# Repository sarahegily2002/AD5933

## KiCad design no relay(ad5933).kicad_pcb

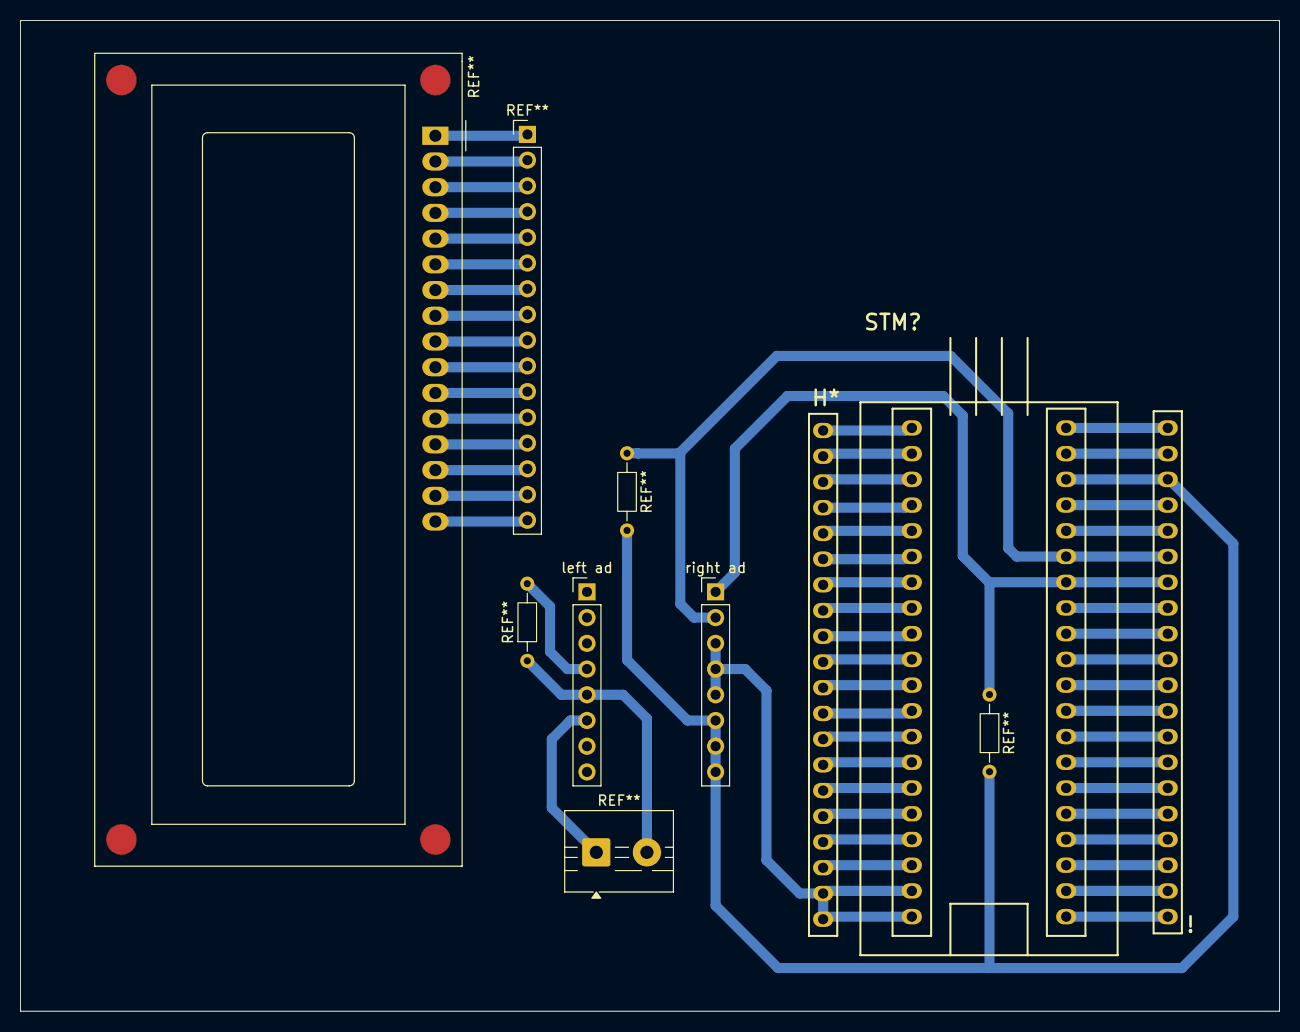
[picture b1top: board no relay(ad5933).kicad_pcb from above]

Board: 2 copper layers, 124.3 x 97.8 mm, 5 parts (0 on the bottom side), 38 nets.

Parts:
H*: FEMALE_HEADER_20; Female_Header_20
STM?: STM32
i: FEMALE_HEADER_20; Female_Header_20
left ad: 2; PinHeader_1x08_P2.54mm_Vertical
right ad: 1; PinHeader_1x08_P2.54mm_Vertical

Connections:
NetH*_1: H*.1, H*.2, STM?.GND, i.2, right ad.GND
NetH*_3: H*.3, STM?.3V3
NetH*_4: H*.4, STM?.RES
NetH*_5: H*.5, STM?.PB_11
NetH*_6: H*.6, STM?.PB_10
NetH*_7: H*.7, STM?.PB_1
NetH*_8: H*.8, STM?.PB_0
NetH*_9: H*.9, STM?.PA_7
NetH*_10: H*.10, STM?.PA_6
NetH*_11: H*.11, STM?.PA_5
NetH*_12: H*.12, STM?.PA_4
NetH*_13: H*.13, STM?.PA_3
NetH*_14: H*.14, STM?.PA_2
NetH*_15: H*.15, STM?.PA_1
NetH*_16: H*.16, STM?.PA_0
NetH*_17: H*.17, STM?.PC_15
NetH*_18: H*.18, STM?.PC_14
NetH*_19: H*.19, STM?.PC_13
NetH*_20: H*.20, STM?.VBT
Neti_1: STM?.3V3, i.1
Neti_3: STM?.5V, i.3, right ad.5v
Neti_4: STM?.PB_9, i.4
Neti_5: STM?.PB_8, i.5
Neti_6: STM?.PB_7, i.6, right ad.SDA
Neti_7: STM?.PB_6, i.7, right ad.SCL
Neti_8: STM?.PB-5, i.8
Neti_9: STM?.PB-4, i.9
Neti_10: STM?.PB_3, i.10
Neti_11: STM?.PA_15, i.11
Neti_12: STM?.PA_12, i.12
Neti_13: STM?.PA_11, i.13
Neti_14: STM?.PA_10, i.14
Neti_15: STM?.PA_9, i.15
Neti_16: STM?.PA_8, i.16
Neti_17: STM?.PB_15, i.17
Neti_18: STM?.PB_14, i.18
Neti_19: STM?.PB_13, i.19
Neti_20: STM?.PB_12, i.20

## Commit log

2025-05-11 Create ll
